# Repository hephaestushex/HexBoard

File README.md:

# HexBoard

A wireless split keyboard designed by HephaestusHex. It uses the SEEED Studio XIAO nRF52840 for wireless bluetooth connectivity

I made this split keyboard because it was a great project for learning PCB design, ergonomics, case design, keyboard firmware, and more. I wanted to make a split keyboard specifically because during my research, I found it's better than a regular keyboard because of ergonomics that I won't get into. Ben Vallack has [videos](https://www.youtube.com/@BenVallack) that gets into the details.

# YouTube Demo

Access the youtube demo [here](https://www.youtube.com/watch?v=F45BFvxeQR0)

# CAD
## PCB

## Case

# Firmware

This kb uses ZMK for firmware. Due to ZMK's requirement of using another repo, all of the zmk code is in this [repo](https://github.com/hephaestushex/zmk-config-hexboard)

# BOM

| Name | Reference | Quantity | Value | Footprint | Part Link | Description | Price (USD) |
| --- | --- | --- | --- | --- | --- | --- | --- |
| 1N4148 Diodes | D1-18 | 36 | 1N4148 | D_DO-35_SOD27_P7.62mm_Horizontal | [AliExpress](https://www.aliexpress.us/item/1005004962400215.html) | Used for switch matrix | $1.01 |
| Gateron KS-33 Low Profile Switches | SW1-18 | 36 |  | Gateron-KS33-Solderable-1U | [AliExpress](https://www.aliexpress.us/item/1005006637645158.html) | Low-profile switches | $25.22 |
| Seeed XIAO nRF52840 | U1 | 2 |  | XIAO-nRF52840-DIP-Batt | [AliExpress](https://www.aliexpress.us/item/1005008484816031.html) | Bluetooth MCU for wireless split connectivity | $31.09 |
| 601730 3.7V LiPo Battery | J1 | 2 | 250mAh | PinHeader_1x02_P2.54mm_Vertical | [AliExpress](https://www.aliexpress.us/item/1005006584143607.html) | Battery for MCU | $5.47 |
| PCB | hexboard-left, hexboard-right | 2 |  |  | [JLC PCB](https://jlcpcb.com/) | PCB for the left and right halves of the keyboard | $24.33 |
| M3x5x4 Heatset Inserts |  | 8 |  |  | [AliExpress](https://www.aliexpress.us/item/4000232858343.html) | Heatset inserts for mounting components | $6.23 |
| M3x6 Screws | H1-4 | 8 |  | MountingHole_3.2mm_M3 | [AliExpress](https://www.aliexpress.us/item/32794842281.html) | Screws for securing the PCB to the case | $2.89 |
| Slide SPDT Switches | SW19 | 2 |  | SW_Slide_SPDT_Straight_CK_OS102011MS2Q | [AliExpress](https://www.aliexpress.us/item/1005007162182882.html) | Slide switch for power control | $1.46 |
| Case |  |  |  |  |  | Free since I already have filament | $2.78 |
| Keycaps |  |  |  |  |  | Free since I already have filament | $0.66 |
| AliExpress Total  |  |  |  |  |  |  | $75.80 |
| JLCPCB Total  |  |  |  |  |  |  | $30.80 |
| Grand Total |  |  |  |  |  |  | $113.04 |

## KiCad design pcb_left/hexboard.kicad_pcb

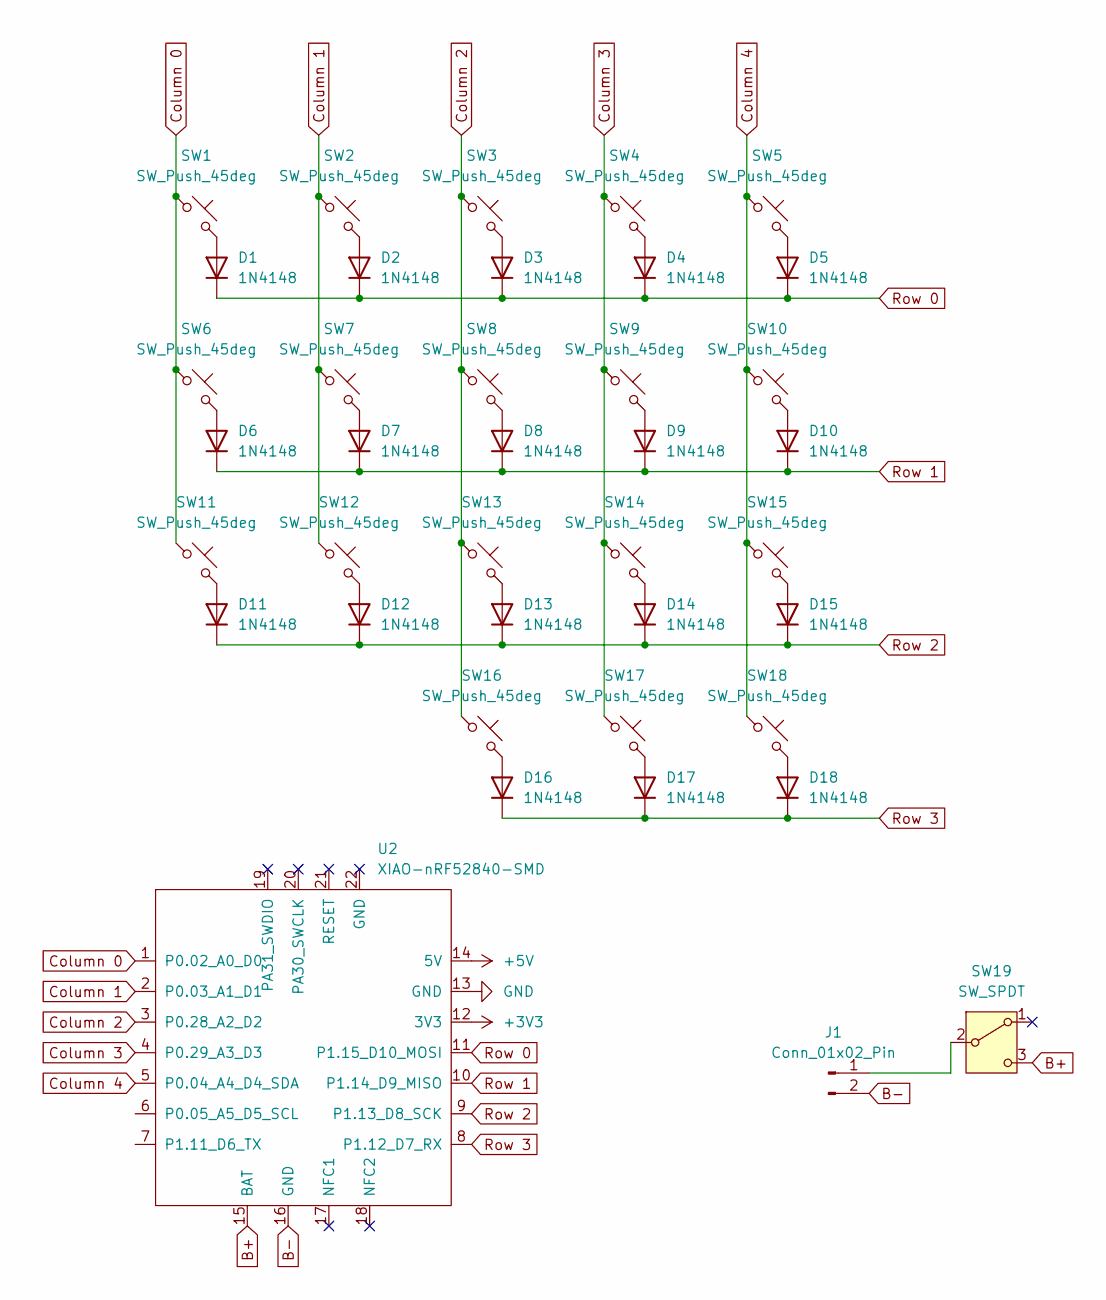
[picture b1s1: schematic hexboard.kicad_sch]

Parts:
D1, D2, D3, D4, D5, D6, D7, D8, D9, D10, D11, D12, D13, D14, D15, D16, D17, D18: 1N4148; D_DO-35_SOD27_P7.62mm_Horizontal
J1: Conn_01x02_Pin; PinHeader_1x02_P2.54mm_Vertical
SW1, SW2, SW3, SW4, SW5, SW6, SW7, SW8, SW9, SW10, SW11, SW12, SW13, SW14, SW15, SW16, SW17, SW18: SW_Push_45deg; Gateron-KS33-Solderable-1U
SW19: SW_SPDT; SW_Slide_SPDT_Straight_CK_OS102011MS2Q
U2: XIAO-nRF52840-SMD; XIAO-nRF52840-DIP-Batt

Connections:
+3V3: U2.12 (3V3)
+5V: U2.14 (5V)
B+: SW19.3 (C), U2.15 (BAT)
B-: J1.2, U2.16 (GND)
Column 0: SW1.1, SW6.1, SW11.1, U2.1 (P0.02_A0_D0)
Column 1: SW2.1, SW7.1, SW12.1, U2.2 (P0.03_A1_D1)
Column 2: SW3.1, SW8.1, SW13.1, SW16.1, U2.3 (P0.28_A2_D2)
Column 3: SW4.1, SW9.1, SW14.1, SW17.1, U2.4 (P0.29_A3_D3)
Column 4: SW5.1, SW10.1, SW15.1, SW18.1, U2.5 (P0.04_A4_D4_SDA)
GND: U2.13 (GND)
unnamed: D1.2 (A), SW1.2
unnamed: D2.2 (A), SW2.2
unnamed: D3.2 (A), SW3.2
unnamed: D4.2 (A), SW4.2
unnamed: D5.2 (A), SW5.2
unnamed: D6.2 (A), SW6.2
unnamed: D7.2 (A), SW7.2
unnamed: D8.2 (A), SW8.2
unnamed: D9.2 (A), SW9.2
unnamed: D10.2 (A), SW10.2
unnamed: D11.2 (A), SW11.2
unnamed: D12.2 (A), SW12.2
unnamed: D13.2 (A), SW13.2
unnamed: D14.2 (A), SW14.2
unnamed: D15.2 (A), SW15.2
unnamed: D16.2 (A), SW16.2
unnamed: D17.2 (A), SW17.2
unnamed: D18.2 (A), SW18.2
unnamed: J1.1, SW19.2 (B)
Row 0: D1.1 (K), D2.1 (K), D3.1 (K), D4.1 (K), D5.1 (K), U2.11 (P1.15_D10_MOSI)
Row 1: D6.1 (K), D7.1 (K), D8.1 (K), D9.1 (K), D10.1 (K), U2.10 (P1.14_D9_MISO)
Row 2: D11.1 (K), D12.1 (K), D13.1 (K), D14.1 (K), D15.1 (K), U2.9 (P1.13_D8_SCK)
Row 3: D16.1 (K), D17.1 (K), D18.1 (K), U2.8 (P1.12_D7_RX)

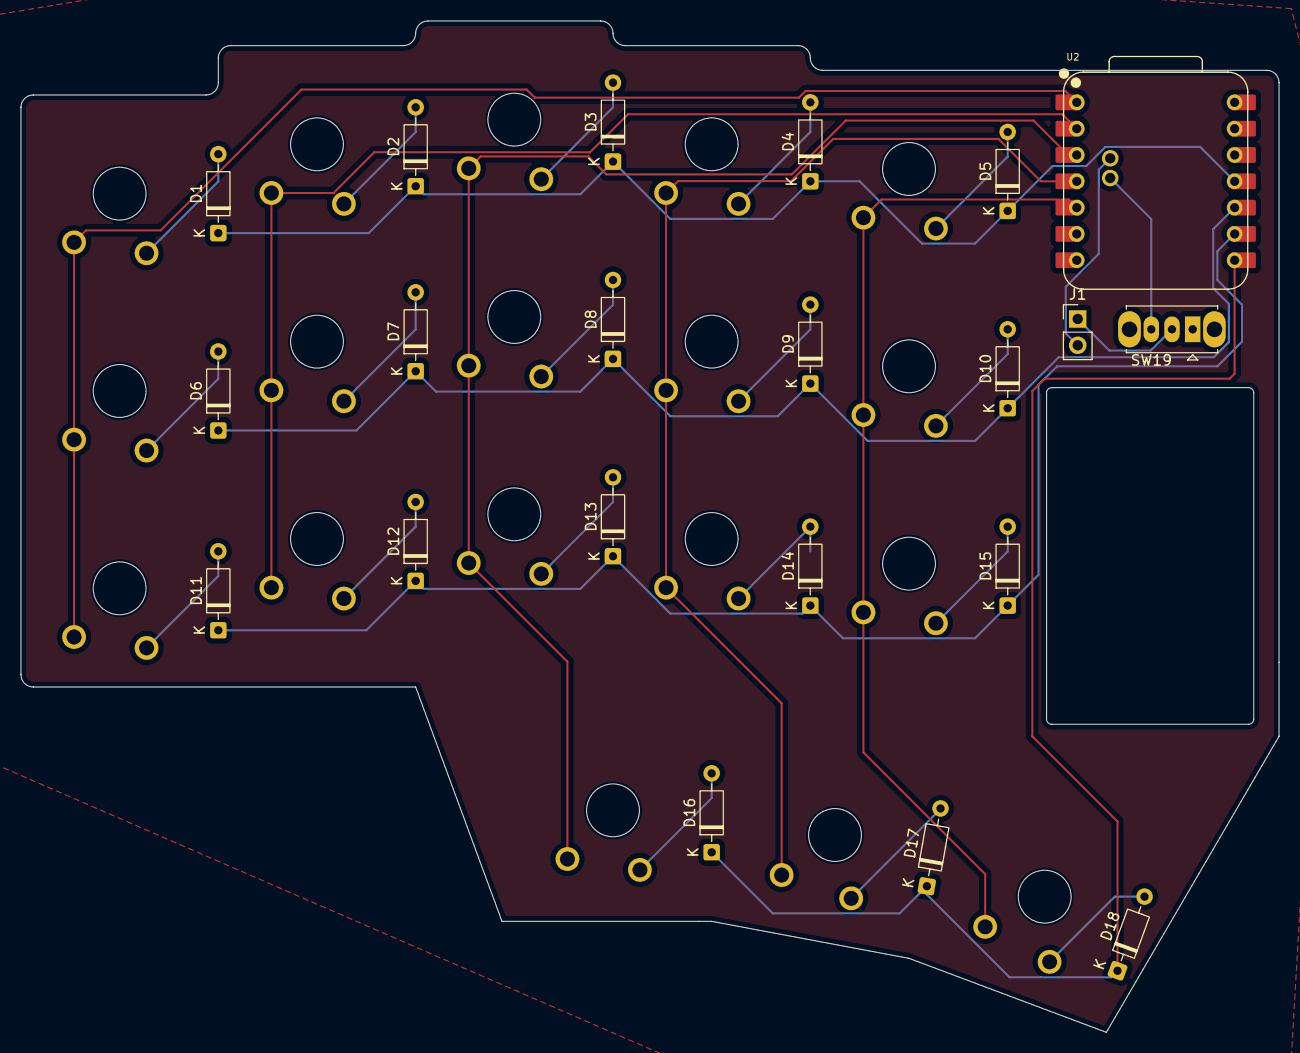
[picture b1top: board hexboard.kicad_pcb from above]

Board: 2 copper layers, 121.4 x 97.6 mm, 39 parts (0 on the bottom side), 30 nets.

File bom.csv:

Name,Reference,Quantity,Value,Footprint,Part Link,Description,Price (USD)
1N4148 Diodes,"D1, D2, D3, D4, D5, D6, D7, D8, D9, D10, D11, D12, D13, D14, D15, D16, D17, D18",36,1N4148,D_DO-35_SOD27_P7.62mm_Horizontal,https://www.aliexpress.us/item/1005004962400215.html,Used for switch matrix,$1.01
Gateron KS-33 Low Profile Switches,"SW1, SW2, SW3, SW4, SW5, SW6, SW7, SW8, SW9, SW10, SW11, SW12, SW13, SW14, SW15, SW16, SW17, SW18",36,,Gateron-KS33-Solderable-1U,https://www.aliexpress.us/item/1005006637645158.html,Low-profile switches,$25.22
Seeed XIAO nRF52840,"U1",2,,XIAO-nRF52840-DIP-Batt,https://www.aliexpress.us/item/1005008484816031.html,Bluetooth MCU for wireless split connectivity,$31.09
502030 3.7V LiPo Battery,"J1",2,250mAh,PinHeader_1x02_P2.54mm_Vertical,https://www.aliexpress.us/item/1005006584143607.html,Battery for MCU,$5.47
PCB,"hexboard-left, hexboard-right",2,,,https://jlcpcb.com/,PCB for the left and right halves of the keyboard,$24.33
M3x5x4 Heatset Inserts,,8,,,https://www.aliexpress.us/item/4000232858343.html,Heatset inserts for mounting components,$6.23
M3x6 Screws,,8,,,https://www.aliexpress.us/item/32794842281.html,Screws for securing the PCB to the case,$2.89
Slide SPDT Switches,"SW19",2,,SW_Slide_SPDT_Straight_CK_OS102011MS2Q,https://www.aliexpress.us/item/1005007162182882.html,Slide switch for power control,$1.46
Total,,,,,,,$97.7

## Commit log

2025-06-05 Create journal setup
2025-06-12 Added PCB and the BOM
2025-06-12 Part of day 12 journal
2025-06-12 Added PCB images and BOM
2025-06-13 Updated PCB
2025-06-17 updated folder structure, remove screw holes
2025-06-18 Added STEP files for the case, both halves
2025-06-19 added firmware
2025-06-19 Created a production folder
2025-06-19 Committing any uncommitted changes
2025-06-20 Update README.md to reflect case and keycap cost
2025-06-24 Update README.md to show render
2025-06-24 added design to case, colorized 3mf files
2025-06-25 update pcb if necessary
2025-08-25 added files
